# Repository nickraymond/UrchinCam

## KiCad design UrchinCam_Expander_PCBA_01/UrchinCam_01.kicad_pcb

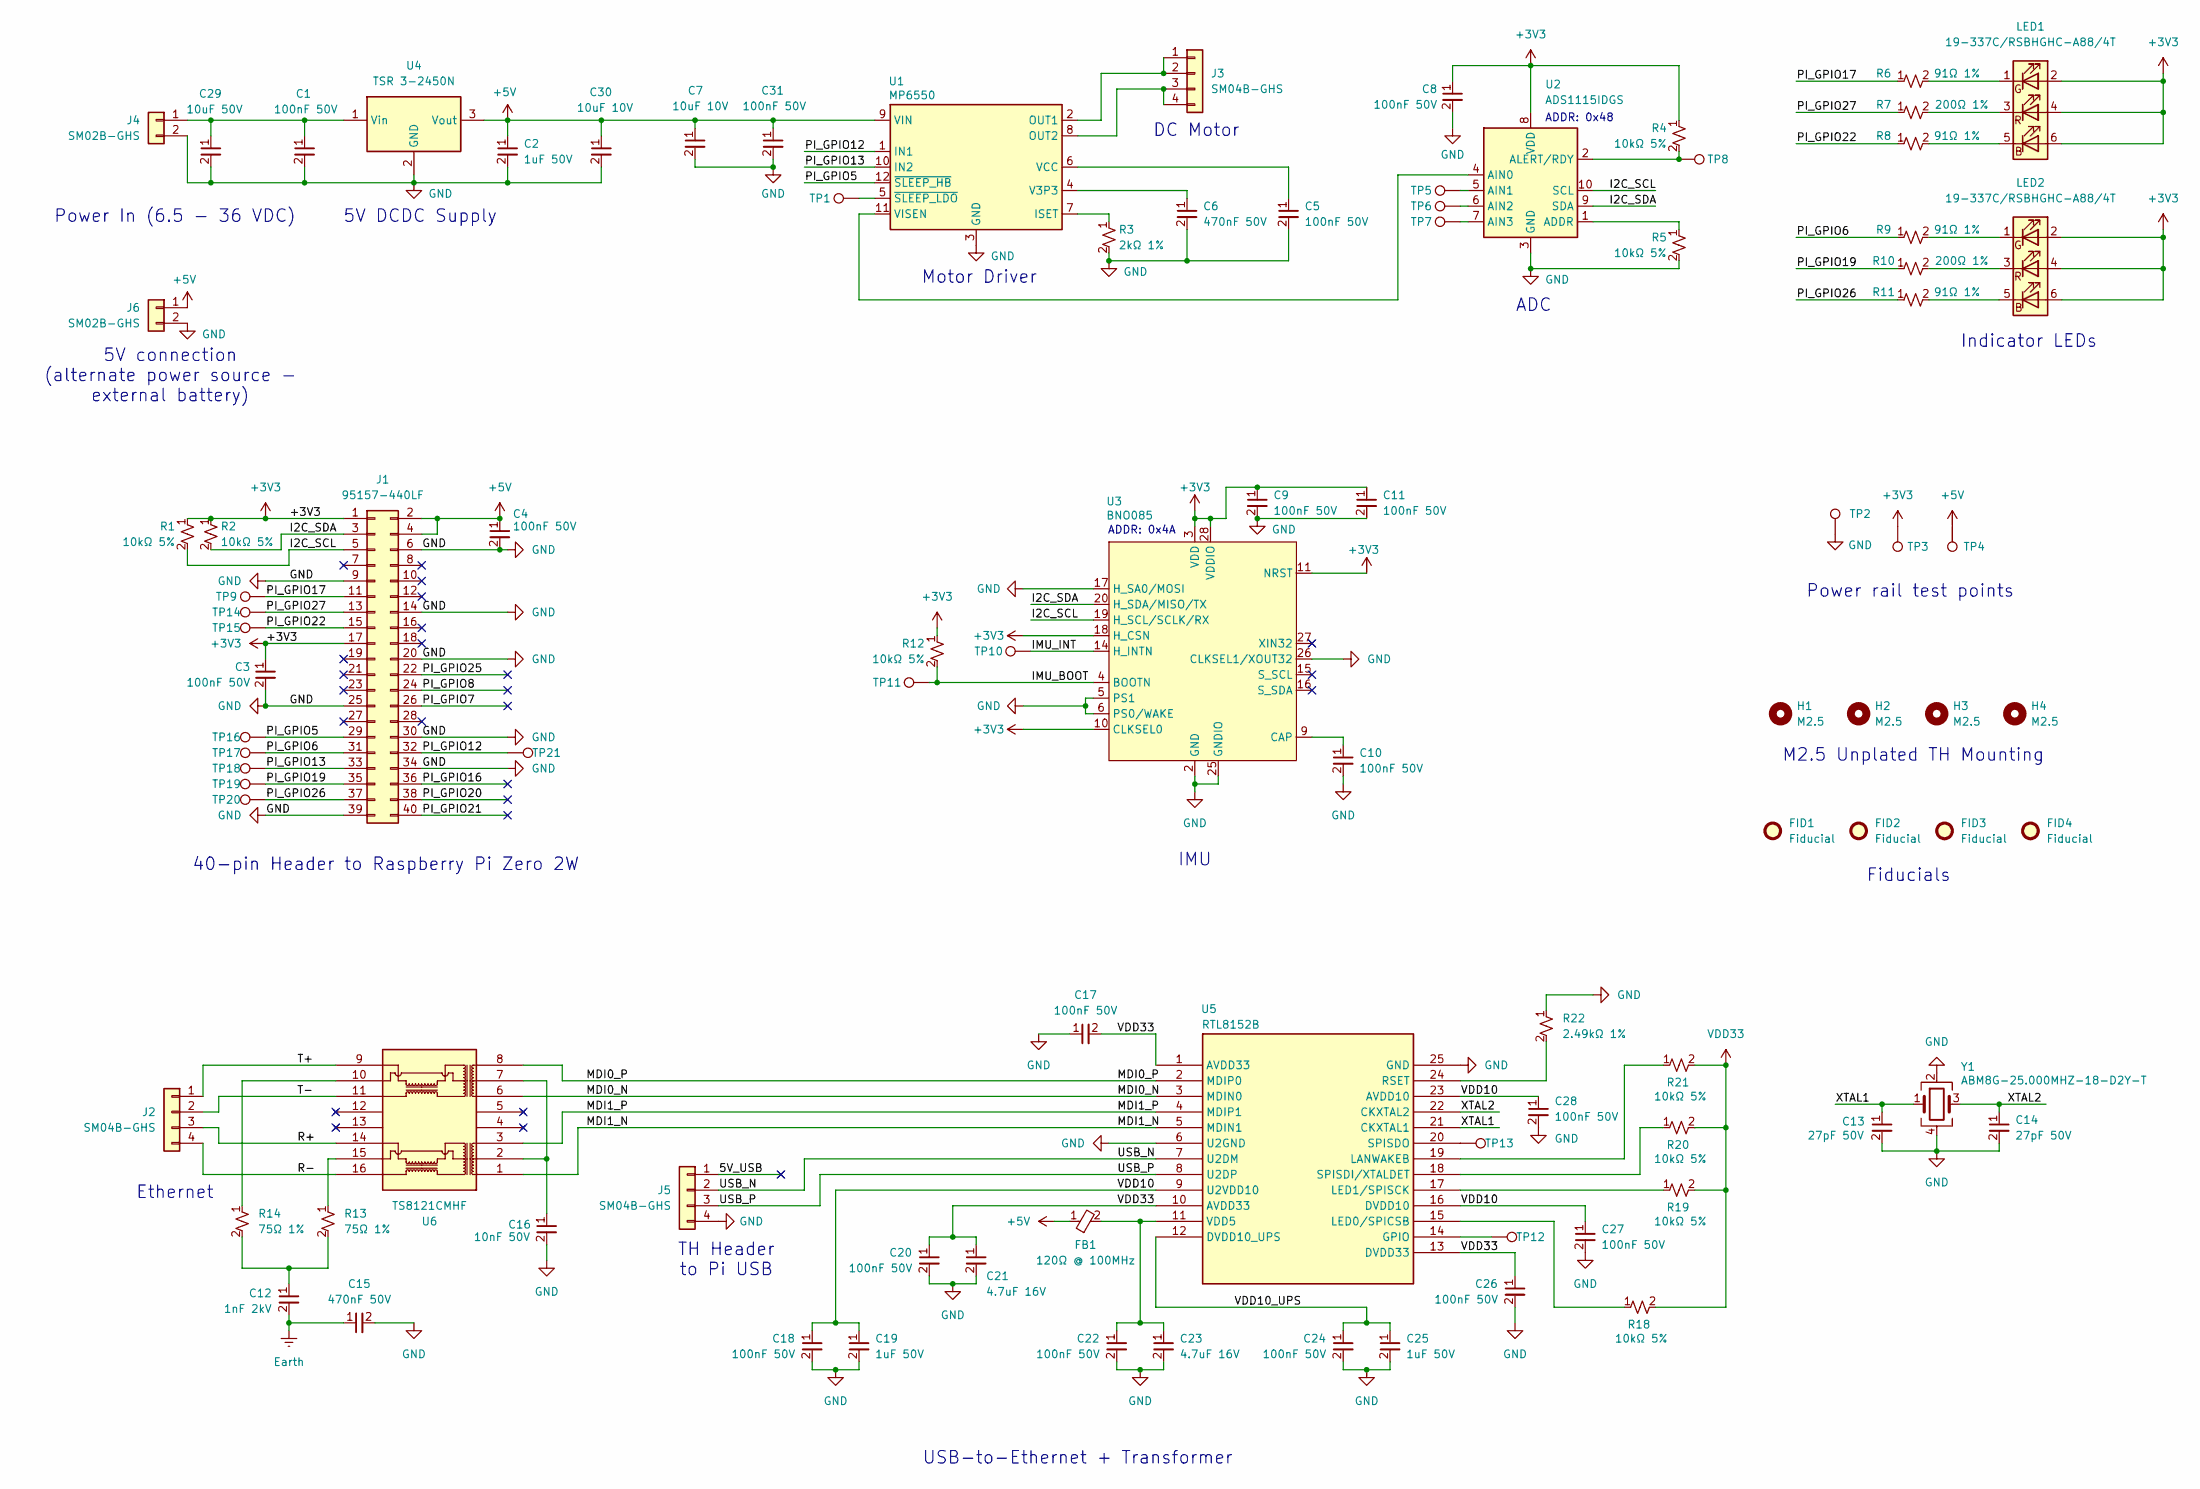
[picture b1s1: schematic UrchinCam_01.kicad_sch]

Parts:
C1, C3, C4, C5, C8, C9, C10, C11, C17, C18, C20, C22, C24, C26, C27, C28, C31: 100nF 50V; C_0402_1005Metric_Pad0.74x0.62mm_HandSolder
C2, C19, C25: 1uF 50V; C_0402_1005Metric_Pad0.74x0.62mm_HandSolder
C6, C15: 470nF 50V; C_0402_1005Metric_Pad0.74x0.62mm_HandSolder
C7, C30: 10uF 10V; C_0402_1005Metric_Pad0.74x0.62mm_HandSolder
C12: 1nF 2kV; C_1206_3216Metric_Pad1.33x1.80mm_HandSolder
C13, C14: 27pF 50V; C_0402_1005Metric_Pad0.74x0.62mm_HandSolder
C16: 10nF 50V; C_0402_1005Metric_Pad0.74x0.62mm_HandSolder
C21, C23: 4.7uF 16V; C_0402_1005Metric_Pad0.74x0.62mm_HandSolder
C29: 10uF 50V; C_0805_2012Metric_Pad1.18x1.45mm_HandSolder
FB1: 120Ω @ 100MHz; R_0402_1005Metric_Pad0.72x0.64mm_HandSolder
FID1, FID2, FID3, FID4: Fiducial; Fiducial_0.5mm_Mask1mm
H1, H2, H3, H4: M2.5; M2.5_Mounting_Hole_2.9mm_unplated
J1: 95157-440LF; Amphenol_95157-440LF_2x20_P2.54mm_Vertical
J2, J3, J5: SM04B-GHS; JST_GH_SM04B-GHS-TB_1x04-1MP_P1.25mm_Horizontal
J4, J6: SM02B-GHS; JST_GH_SM02B-GHS-TB_1x02-1MP_P1.25mm_Horizontal
LED1, LED2: 19-337C/RSBHGHC-A88/4T; 19-337C RSBHGHC-A88 4T
R1, R2, R4, R5, R12, R18, R19, R20, R21: 10kΩ 5%; R_0402_1005Metric_Pad0.72x0.64mm_HandSolder
R3: 2kΩ 1%; R_0402_1005Metric_Pad0.72x0.64mm_HandSolder
R6, R8, R9, R11: 91Ω 1%; R_0603_1608Metric_Pad0.98x0.95mm_HandSolder
R7, R10: 200Ω 1%; R_0603_1608Metric_Pad0.98x0.95mm_HandSolder
R13, R14: 75Ω 1%; R_0402_1005Metric_Pad0.72x0.64mm_HandSolder
R22: 2.49kΩ 1%; R_0402_1005Metric_Pad0.72x0.64mm_HandSolder
TP1, TP2, TP3, TP4, TP5, TP6, TP7, TP8, TP9, TP10, TP11, TP12, TP13, TP14, TP15, TP16, TP17, TP18, TP19, TP20, TP21: TestPoint; TestPoint_Pad_D1.5mm
U1: MP6550; MP6550GG
U2: ADS1115IDGS; TSSOP-10_3x3mm_P0.5mm
U3: BNO085; LGA-28_5.2x3.8mm_P0.5mm
U4: TSR 3-2450N; Traco_TSR 3-2450N
U5: RTL8152B
U6: TS8121CMHF; TS8121CM HF
Y1: ABM8G-25.000MHZ-18-D2Y-T; Crystal_SMD_3225-4Pin_3.2x2.5mm

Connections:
+3V3: C3.1, C8.1, C9.1, C11.1, J1.1, J1.17, LED1.2 (GA), LED1.4 (RA), LED1.6 (BA), LED2.2 (GA), LED2.4 (RA), LED2.6 (BA), R1.1, R2.1, R4.1, R12.1, TP3.1, U2.8 (VDD), U3.3 (VDD), U3.10 (CLKSEL0), U3.11 (NRST), U3.18 (H_CSN), U3.28 (VDDIO)
+5V: C2.1, C4.1, C7.1, C30.1, C31.1, FB1.1, J1.2, J1.4, J6.1, TP4.1, U1.9 (VIN), U4.3 (Vout)
/5V_USB: J5.1
/I2C_SCL: J1.5, R1.2, U2.10 (SCL), U3.19 (H_SCL/SCLK/RX)
/I2C_SDA: J1.3, R2.2, U2.9 (SDA), U3.20 (H_SDA/MISO/TX)
/IMU_BOOT: R12.2, TP11.1, U3.4 (BOOTN)
/IMU_INT: TP10.1, U3.14 (H_INTN)
/MDI0_N: U5.3 (MDIN0), U6.6
/MDI0_P: U5.2 (MDIP0), U6.8
/MDI1_N: U5.5 (MDIN1), U6.1
/MDI1_P: U5.4 (MDIP1), U6.3
/PI_GPIO5: J1.29, TP16.1, U1.12 (~SLEEP_HB)
/PI_GPIO6: J1.31, R9.1, TP17.1
/PI_GPIO7: J1.26
/PI_GPIO8: J1.24
/PI_GPIO12: J1.32, TP21.1, U1.1 (IN1)
/PI_GPIO13: J1.33, TP18.1, U1.10 (IN2)
/PI_GPIO16: J1.36
/PI_GPIO17: J1.11, R6.1, TP9.1
/PI_GPIO19: J1.35, R10.1, TP19.1
/PI_GPIO20: J1.38
/PI_GPIO21: J1.40
/PI_GPIO22: J1.15, R8.1, TP15.1
/PI_GPIO25: J1.22
/PI_GPIO26: J1.37, R11.1, TP20.1
/PI_GPIO27: J1.13, R7.1, TP14.1
/R+: J2.3, U6.14
/R-: J2.4, U6.16
/T+: J2.1, U6.9
/T-: J2.2, U6.11
/USB_N: J5.2, U5.7 (U2DM)
/USB_P: J5.3, U5.8 (U2DP)
/VDD10: C18.1, C19.1, C27.1, C28.1, U5.9 (U2VDD10), U5.16 (DVDD10), U5.23 (AVDD10)
/VDD10_UPS: C24.1, C25.1, U5.12 (DVDD10_UPS)
/XTAL1: C13.1, U5.21 (CKXTAL1), Y1.1
/XTAL2: C14.1, U5.22 (CKXTAL2), Y1.3
Earth: C12.2, C15.1
GND: C1.2, C2.2, C3.2, C4.2, C5.2, C6.2, C7.2, C8.2, C9.2, C10.2, C11.2, C13.2, C14.2, C15.2, C16.2, C17.1, C18.2, C19.2, C20.2, C21.2, C22.2, C23.2, C24.2, C25.2, C26.2, C27.2, C28.2, C29.2, C30.2, C31.2, J1.6, J1.9, J1.14, J1.20, J1.25, J1.30, J1.34, J1.39, J4.2, J5.4, J6.2, R3.2, R5.2, R22.1, TP2.1, U1.3 (GND), U2.3 (GND), U3.2 (GND), U3.5 (PS1), U3.6 (PS0/WAKE), U3.17 (H_SA0/MOSI), U3.25 (GNDIO), U3.26 (CLKSEL1/XOUT32), U4.2 (GND), U5.6 (U2GND), U5.25 (GND), Y1.2, Y1.4
unnamed: C12.1, R13.2, R14.2
unnamed: C16.1, U6.2, U6.7
unnamed: J3.1, J3.2, U1.2 (OUT1)
unnamed: J3.3, J3.4, U1.8 (OUT2)
unnamed: C1.1, C29.1, J4.1, U4.1 (Vin)
unnamed: LED1.5 (BK), R8.2
unnamed: LED1.1 (GK), R6.2
unnamed: LED1.3 (RK), R7.2
unnamed: LED2.5 (BK), R11.2
unnamed: LED2.1 (GK), R9.2
unnamed: LED2.3 (RK), R10.2
unnamed: R13.1, U6.15
unnamed: R14.1, U6.10
unnamed: R3.1, U1.7 (ISET)
unnamed: C6.1, U1.4 (V3P3)
unnamed: C5.1, U1.6 (VCC)
unnamed: U1.11 (VISEN), U2.4 (AIN0)
unnamed: TP1.1, U1.5 (~SLEEP_LDO)
unnamed: R5.1, U2.1 (ADDR)
unnamed: TP5.1, U2.5 (AIN1)
unnamed: TP6.1, U2.6 (AIN2)
unnamed: TP7.1, U2.7 (AIN3)
unnamed: R4.2, TP8.1, U2.2 (ALERT/RDY)
unnamed: C10.1, U3.9 (CAP)
unnamed: TP12.1, U5.14 (GPIO)
unnamed: R21.1, U5.19 (LANWAKEB)
unnamed: R18.1, U5.15 (LED0/SPICSB)
unnamed: R19.1, U5.17 (LED1/SPISCK)
unnamed: R22.2, U5.24 (RSET)
unnamed: R20.1, U5.18 (SPISDI/XTALDET)
unnamed: TP13.1, U5.20 (SPISDO)
unnamed: C22.1, C23.1, FB1.2, U5.11 (VDD5)
VDD33: C17.2, C20.1, C21.1, C26.1, R18.2, R19.2, R20.2, R21.2, U5.1 (AVDD33), U5.10 (AVDD33), U5.13 (DVDD33)

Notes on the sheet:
Ethernet
Power In (6.5 - 36 VDC)
Motor Driver
Power rail test points
DC Motor
ADC
M2.5 Unplated TH Mounting
TH Header to Pi USB
IMU
Indicator LEDs
ADDR: 0x48
5V connection (alternate power source - external battery)
Fiducials
40-pin Header to Raspberry Pi Zero 2W
USB-to-Ethernet + Transformer
ADDR: 0x4A
5V DCDC Supply

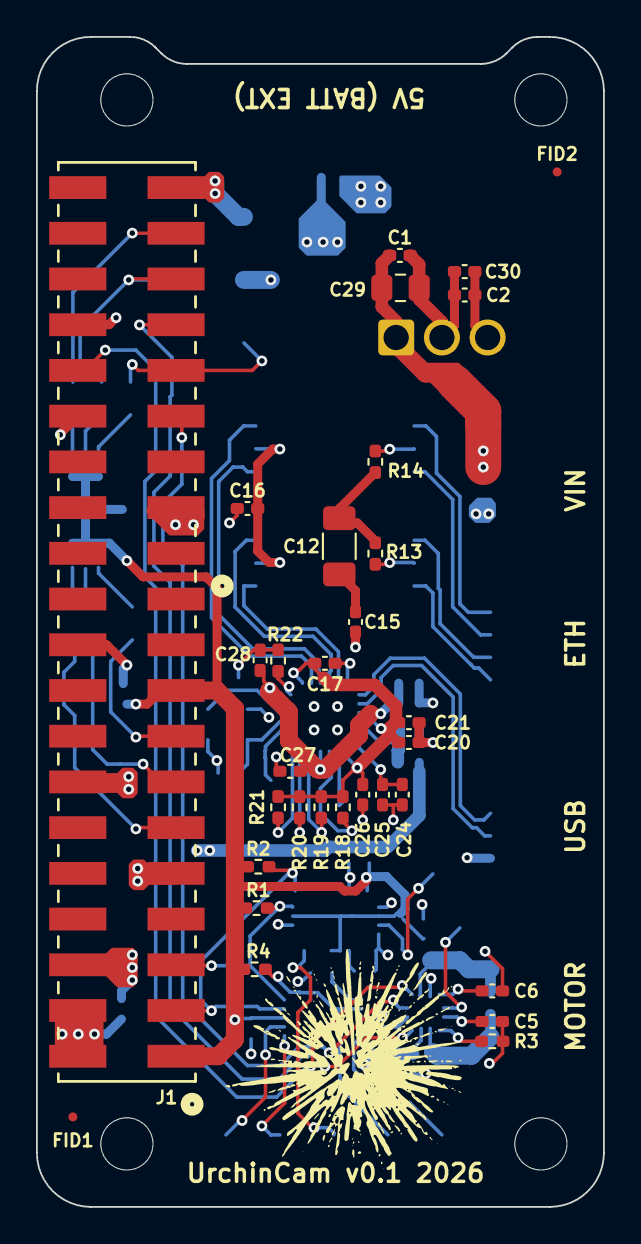
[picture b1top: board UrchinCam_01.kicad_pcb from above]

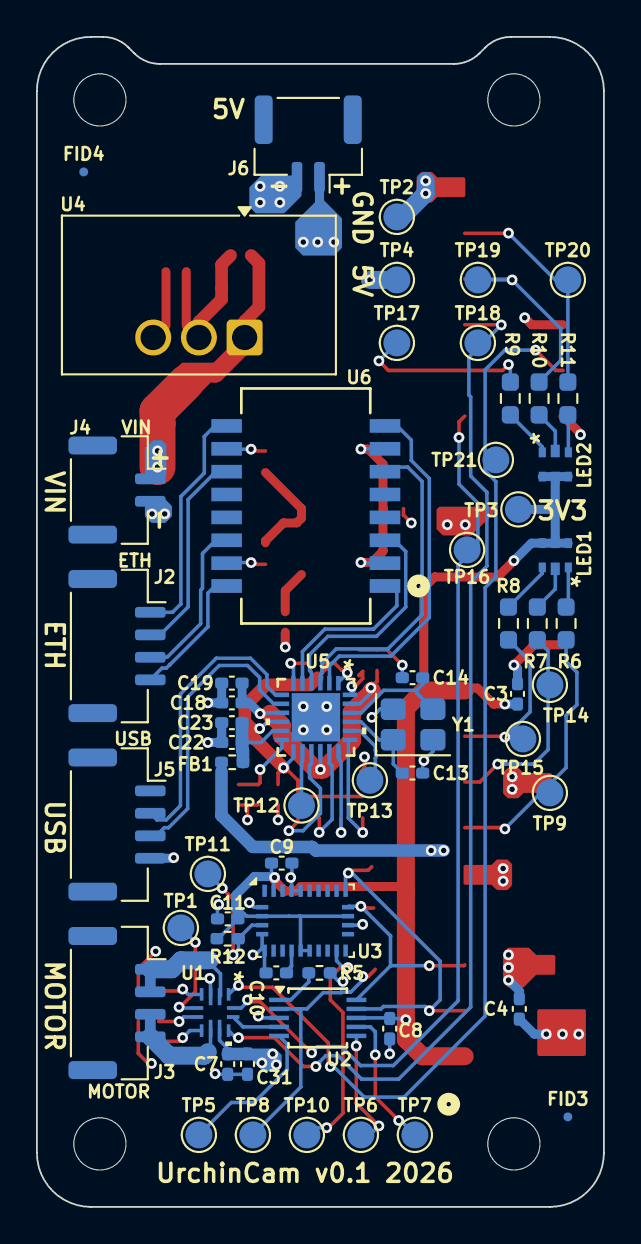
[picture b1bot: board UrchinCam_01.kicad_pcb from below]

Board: 4 copper layers, 31.5 x 65.0 mm, 95 parts (60 on the bottom side), 64 nets.

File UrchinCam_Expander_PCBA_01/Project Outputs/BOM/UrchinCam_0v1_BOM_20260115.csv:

Id,Designator,Footprint,Quantity,Designation,Manufacturer 1,Manufacturer Part Number 1
1,"J6,J4",JST_GH_SM02B-GHS-TB_1x02-1MP_P1.25mm_Horizontal,2,SM02B-GHS,JST,SM02B-GHS
2,C29,C_0805_2012Metric_Pad1.18x1.45mm_HandSolder,1,10uF 50V,Murata,GRM21BR61H106KE43L
3,"C30,C7",C_0402_1005Metric_Pad0.74x0.62mm_HandSolder,2,10uF 10V,Murata,GRM155R61A106ME11D
4,"C1,C28,C5,C27,C24,C26,C17,C20,C22,C11,C8,C10,C9,C3,C18,C31,C4",C_0402_1005Metric_Pad0.74x0.62mm_HandSolder,17,100nF 50V,Yageo,CC0402KRX5R9BB104
5,"C2,C25,C19",C_0402_1005Metric_Pad0.74x0.62mm_HandSolder,3,1uF 50V,Taiyo Yuden,UMK105CBJ105MV-F
6,U4,Traco_TSR 3-2450N,1,TSR 3-2450N,Traco Power,TSR 3-2450N
7,U1,MP6550GG,1,MP6550,Monolithic Power Systems Inc.,MP6550GG
8,U5,RTL8152B,1,RTL8152B,Realtek,RTL8152B
9,R3,R_0402_1005Metric_Pad0.72x0.64mm_HandSolder,1,2kΩ 1%,Vishay Dale,CRCW04022K00FKED
10,"R2,R21,R19,R1,R18,R20,R4,R5,R12",R_0402_1005Metric_Pad0.72x0.64mm_HandSolder,9,10kΩ 5%,Yageo,RC0402JR-0710KL
12,"R14,R13",R_0402_1005Metric_Pad0.72x0.64mm_HandSolder,2,75Ω 1%,Yageo,RC0402FR-0775RL
13,"C21,C23",C_0402_1005Metric_Pad0.74x0.62mm_HandSolder,2,4.7uF 16V,Samsung Electro-Mechanics,CL05A475MO5NUNC
14,C12,C_1206_3216Metric_Pad1.33x1.80mm_HandSolder,1,1nF 2kV,Samsung Electro-Mechanics,CL31B102KJHNNNE
15,"C15,C6",C_0402_1005Metric_Pad0.74x0.62mm_HandSolder,2,470nF 50V,Taiyo Yuden,UMK105ABJ474KV-F
16,J1,Amphenol_95157-440LF_2x20_P2.54mm_Vertical,1,95157-440LF,Amphenol ICC (FCI),95157-440LF
17,C16,C_0402_1005Metric_Pad0.74x0.62mm_HandSolder,1,10nF 50V,Yageo,CC0402KRX7R9BB103
18,R22,R_0402_1005Metric_Pad0.72x0.64mm_HandSolder,1,2.49kΩ 1%,Vishay Dale,CRCW04022K49FKED
19,"J2,J3,J5",JST_GH_SM04B-GHS-TB_1x04-1MP_P1.25mm_Horizontal,3,SM04B-GHS,JST,SM04B-GHS
21,U2,TSSOP-10_3x3mm_P0.5mm,1,ADS1115IDGS,Texas Instruments,ADS1115IDGS
22,FB1,R_0402_1005Metric_Pad0.72x0.64mm_HandSolder,1,120Ω @ 100MHz,Murata,BLM15PD121SN1D
23,"C14,C13",C_0402_1005Metric_Pad0.74x0.62mm_HandSolder,2,27pF 50V,Murata,GRM1555C1H270JA01J
24,"R10,R7",R_0603_1608Metric_Pad0.98x0.95mm_HandSolder,2,200Ω 1%,Vishay Dale,CRCW0603200RFKEA
25,"R8,R9,R11,R6",R_0603_1608Metric_Pad0.98x0.95mm_HandSolder,4,91Ω 1%,Yageo,RC0603FR-0791RL
26,Y1,Crystal_SMD_3225-4Pin_3.2x2.5mm,1,ABM8G-25.000MHZ-18-D2Y-T,Abracon LLC,ABM8G-25.000MHZ-18-D2Y-T
27,U6,TS8121CM HF,1,TS8121CMHF,Pulse Electronics,TS8121CM HF
28,U3,LGA-28_5.2x3.8mm_P0.5mm,1,BNO085,"CEVA Technologies, Inc.",BNO085
29,"LED2,LED1",19-337C RSBHGHC-A88 4T,2,19-337C/RSBHGHC-A88/4T,Everlight Electronics Co Ltd,19-337C/RSBHGHC-A88/4T

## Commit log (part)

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2026-01-12 Camera Expander PCBA
    Adding Camera Expander PCBA KiCad project.
2026-01-12 Changed TH USB conn to JST.
2026-01-13 Layout - placing tall components.
2026-01-13 Layout - routing ethernet + magnetics.
2026-01-14 All components except test points positioned.
2026-01-14 Routing done!
2026-01-14 First pass complete!
2026-01-14 Fixed all DRC errors.
2026-01-15 Added header STEP model.
2026-01-15 Fixing ethernet routing.
2026-01-15 Fixing via diameters.
2026-01-15 Adding DCDC model.
2026-01-15 Added LED 3D model.
2026-01-15 Added ethernet transformer STEP model.
2026-01-16 Incorporated feedback from meeting.
2026-01-16 Uploading BOM.
2026-01-16 Last edits!
2026-01-16 Gerbers, BOM, NC Drill, and Pick & Place generated for JLPCB upload.
2026-01-21 Modifying BOM to match available JLPCB parts.
